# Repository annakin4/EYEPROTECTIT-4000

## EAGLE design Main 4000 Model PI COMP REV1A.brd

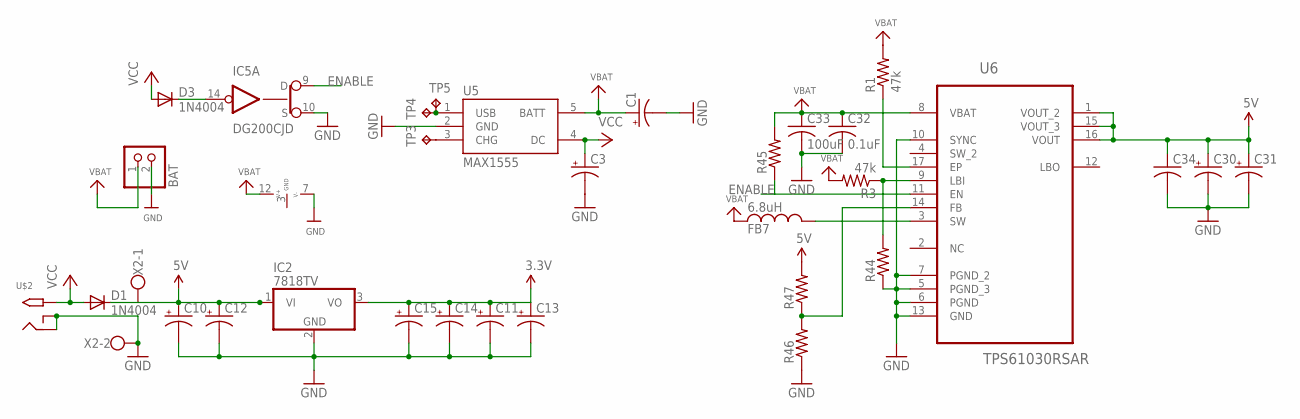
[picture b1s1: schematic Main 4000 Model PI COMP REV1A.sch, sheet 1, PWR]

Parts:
BAT: JST_2PIN-SMT-RA; JST-PH-2-SMT-RA
C1, C3, C11, C12, C14, C15, C30, C31: CPOL-USE1.8-4; E1,8-4
C10, C13: CPOL-USE2.5-6; E2,5-6
C32: 0.1uF; C0805
C33: 100uF; C0805
C34: C-USC0805; C0805
D1, D3: 1N4004; DO41-10
FB7: 6.8uH; SMD0805-A
IC2: 7818TV; TO220V
IC5: DG200CJD; SO14
R1, R3: 47k; R0805
R44, R45, R46, R47: R-US_R0805; R0805
TP3, TP4, TP5: TPTP20SQ; TP20SQ
U5: MAX1555; SOT23-5
U6: TPS61030RSAR; QFN65P400X400X100-17N
U$2: 2.1MMJACKTHM; PJ-102A
X2: W237-102

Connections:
3.3V: C11.+, C13.+, C14.+, C15.+, IC2.3 (VO); also elsewhere on the board
5V: C10.+, C12.+, C30.+, C31.+, C34.1, D1.C, IC2.1 (VI), R47.2, U6.1 (VOUT_2), U6.15 (VOUT_3), U6.16 (VOUT), X2.1; also elsewhere on the board
ENABLE: IC5.9 (D), R45.1, U6.11 (EN)
FB: R46.2, R47.1, U6.14 (FB)
GND: BAT.2 (1), C1.-, C3.-, C10.-, C11.-, C12.-, C13.-, C14.-, C15.-, C30.-, C31.-, C32.2, C33.2, C34.2, IC2.2 (GND), IC5.3 (GND), IC5.7 (V-), IC5.10 (S), R44.1, R46.1, U5.2 (GND), U6.5 (PGND_3), U6.6 (PGND), U6.7 (PGND_2), U6.10 (SYNC), U6.13 (GND), U$2.RING, U$2.RING_SW, X2.2; also elsewhere on the board
unnamed: TP3.TP, U5.3 (CHG)
unnamed: TP4.TP, TP5.TP, U5.1 (USB)
unnamed: D3.C, IC5.14 (IN)
unnamed: FB7.P$2 (2), U6.3 (SW)
unnamed: R1.1, U6.17 (EP)
unnamed: R3.1, R44.2, U6.9 (LBI)
VBAT: BAT.1 (2), C1.+, C32.1, C33.1, FB7.P$1 (1), IC5.12 (V+), R1.2, R3.2, R45.2, U5.5 (BATT), U6.8 (VBAT); also elsewhere on the board
VCC: C3.+, D1.A, D3.A, U5.4 (DC), U$2.TIP

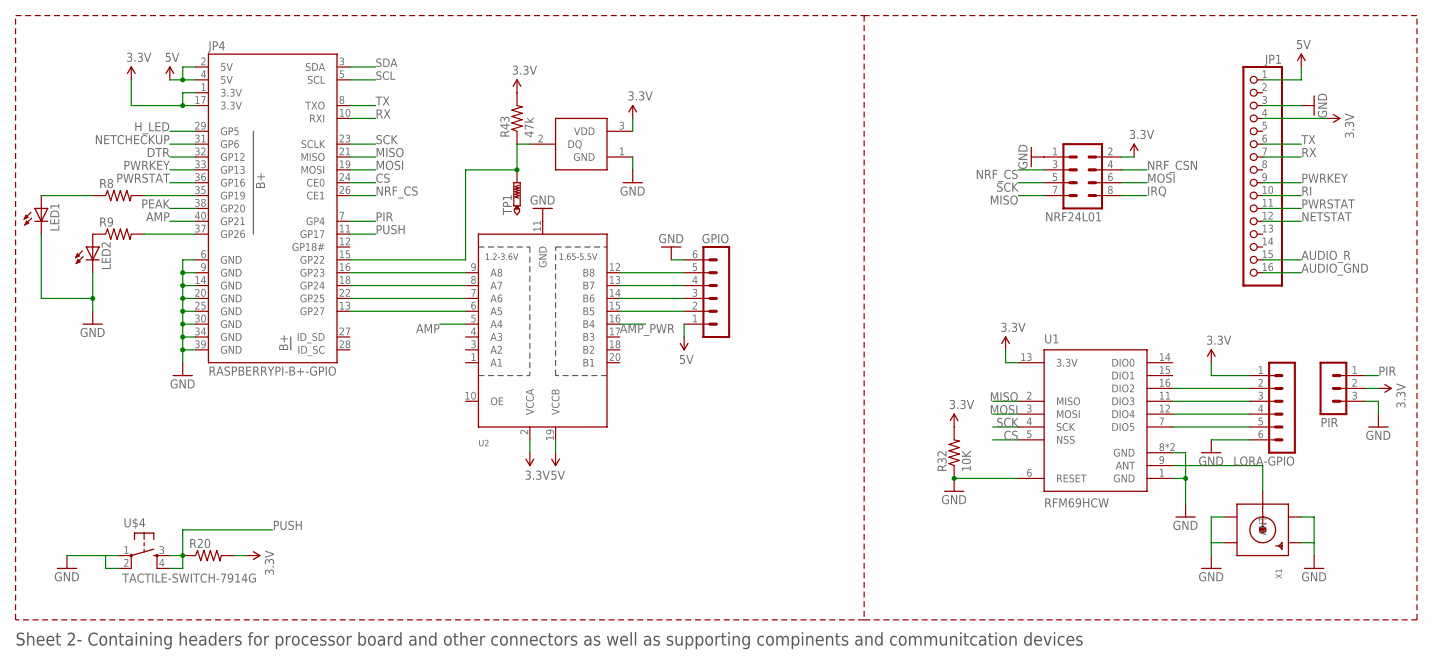
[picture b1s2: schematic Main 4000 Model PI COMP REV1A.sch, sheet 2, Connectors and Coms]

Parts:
GPIO: MA06-1
JP1: PINHD-1X16; 1X16
JP4: RASPBERRYPI-B+-GPIO; 2X20-SHROUDED
LED1, LED2: LED5MM
LORA-GPIO: MA06-1
NRF24L01: MA04-2
PIR: MA03-1
R8, R9, R20: R-US_R0805; R0805
R32: 10K; R0805
R43: 47k; R0805
TP1: PTR1PAD1-13; P1-13
U1: RFM69HCW; RFM69HCW-XXXS2
U2: TXB0108PWR; TSSOP20
U$4: TACTILE-SWITCH-7914G; 7914G
U$11: DS18B20Z; TO92
X1: SMACONNECTOR_EDGE; SMA_EDGELAUNCH

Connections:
3.3V: JP1.4, JP4.1 (3.3V), JP4.17 (3.3V), LORA-GPIO.1, NRF24L01.2, PIR.2, R20.2, R32.2, R43.2, U1.13 (3.3V), U2.2 (VCCA), U$11.3 (VDD); also elsewhere on the board
5V: GPIO.1, JP1.1, JP4.2 (5V), JP4.4 (5V), U2.19 (VCCB); also elsewhere on the board
AMP: JP4.40 (GP21), U2.5 (A4)
AMP_PWR: U2.16 (B4); also elsewhere on the board
AUDIO_GND: JP1.16; also elsewhere on the board
AUDIO_R: JP1.15; also elsewhere on the board
CS: JP4.24 (CE0), U1.5 (NSS)
DTR: JP4.32 (GP12)
GND: GPIO.6, JP1.3, JP4.6 (GND), JP4.9 (GND), JP4.14 (GND), JP4.20 (GND), JP4.25 (GND), JP4.30 (GND), JP4.34 (GND), JP4.39 (GND), LED1.K (C), LED2.K (C), LORA-GPIO.6, NRF24L01.1, PIR.3, R32.1, U1.1 (GND), U1.6 (RESET), U1.8 (GND), U1.10 (GND), U2.11 (GND), U$4.1, U$4.2, U$11.1 (GND), X1.GND@1 (GND4), X1.GND@2 (GND3), X1.GND@3 (GND2), X1.GND@4 (GND1); also elsewhere on the board
H_LED: JP4.29 (GP5); also elsewhere on the board
IRQ: NRF24L01.8
LED1: JP4.35 (GP19), R8.2
LED2: JP4.37 (GP26), R9.2
MISO: JP4.21 (MISO), NRF24L01.7, U1.2 (MISO)
MOSI: JP4.19 (MOSI), NRF24L01.6, U1.3 (MOSI)
unnamed: LORA-GPIO.5, U1.7 (DIO5)
unnamed: U1.9 (ANT), X1.P (ANT)
unnamed: LORA-GPIO.4, U1.12 (DIO4)
unnamed: LORA-GPIO.3, U1.11 (DIO3)
unnamed: LORA-GPIO.2, U1.16 (DIO2)
unnamed: LED2.A, R9.1
unnamed: JP4.16 (GP23), U2.9 (A8)
unnamed: JP4.18 (GP24), U2.8 (A7)
unnamed: JP4.22 (GP25), U2.7 (A6)
unnamed: JP4.13 (GP27), U2.6 (A5)
unnamed: LED1.A, R8.1
unnamed: GPIO.2, U2.15 (B5)
unnamed: GPIO.3, U2.14 (B6)
unnamed: GPIO.4, U2.13 (B7)
unnamed: GPIO.5, U2.12 (B8)
unnamed: JP4.15 (GP22), R43.1, TP1.TP, U$11.2 (DQ)
NETCHECKUP: JP4.31 (GP6)
NETSTAT: JP1.12
NRF_CS: JP4.26 (CE1), NRF24L01.3
NRF_CSN: NRF24L01.4
PEAK: JP4.38 (GP20); also elsewhere on the board
PIR: JP4.7 (GP4), PIR.1
PUSH: JP4.11 (GP17), R20.1, U$4.3, U$4.4
PWRKEY: JP1.9, JP4.33 (GP13)
PWRSTAT: JP1.11, JP4.36 (GP16)
RI: JP1.10
RX: JP1.7, JP4.10 (RXI)
SCK: JP4.23 (SCLK), NRF24L01.5, U1.4 (SCK)
SCL: JP4.5 (SCL); also elsewhere on the board
SDA: JP4.3 (SDA); also elsewhere on the board
TX: JP1.6, JP4.8 (TXO)

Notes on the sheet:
Sheet 2- Containing headers for processor board and other connectors as well as supporting compinents and communitcation devices

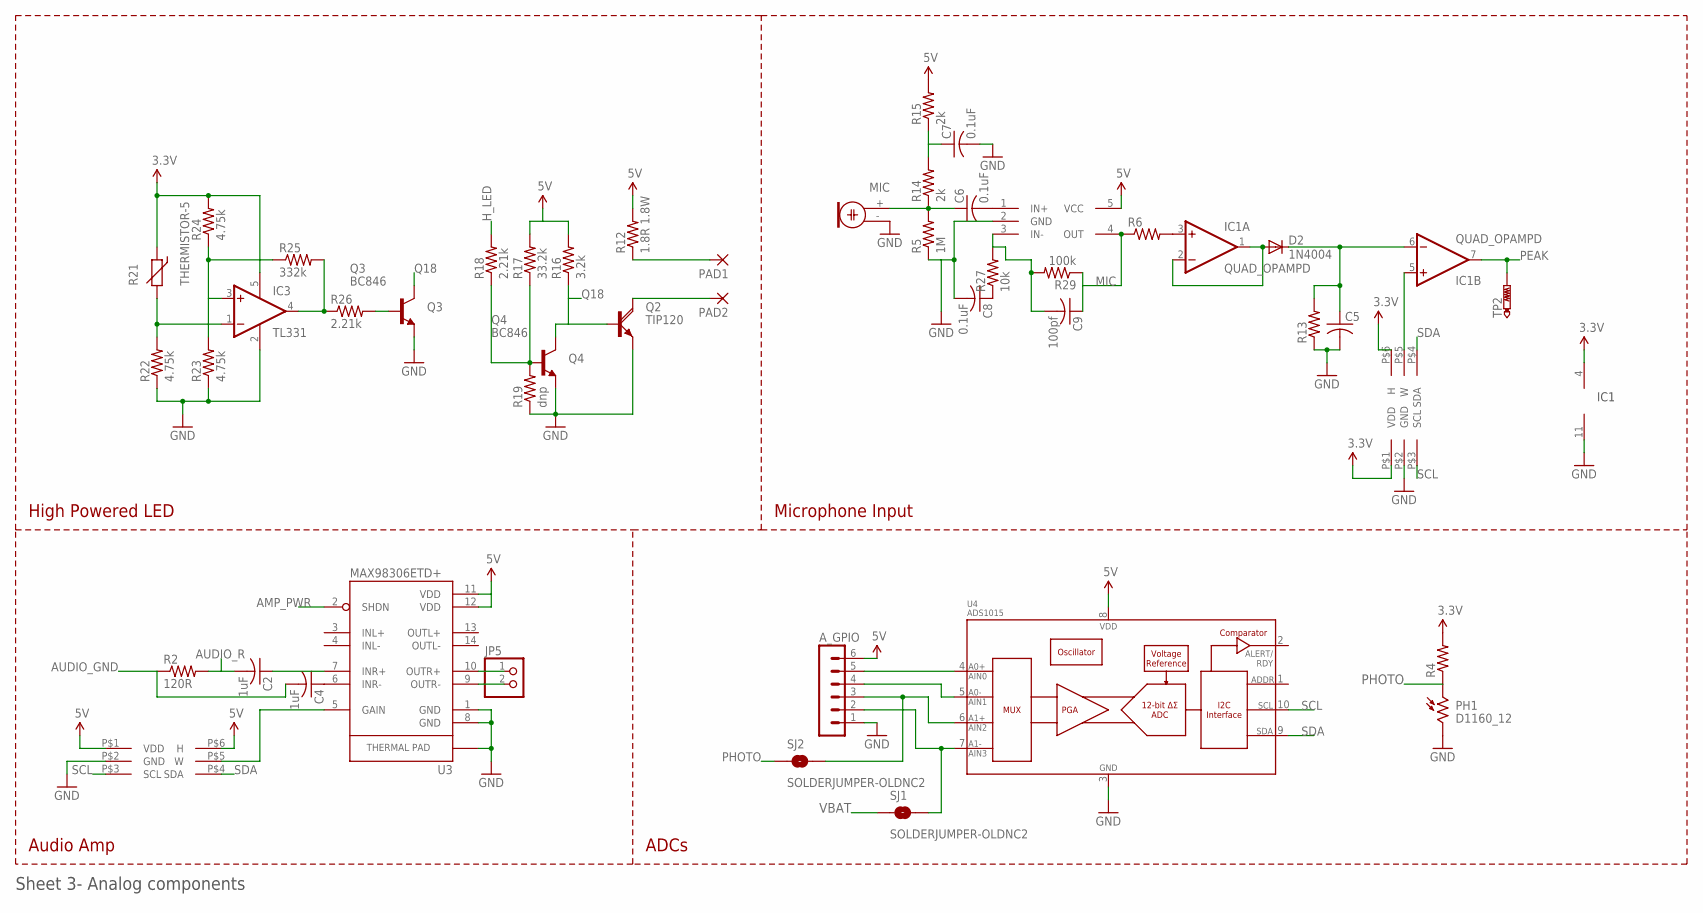
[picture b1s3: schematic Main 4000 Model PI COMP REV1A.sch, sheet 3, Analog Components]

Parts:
A_GPIO: MA06-1
C2, C4: 1uF; C0805
C5: C-USC0805K; C0805K
C6, C7, C8: 0.1uF; C0805
C9: 100pf; C0805
D2: 1N4004; DO41-10
IC1: QUAD_OPAMPD; SO14
IC3: TL331; DBV-R-PDSO-G5
JP5: PINHD-1X2; 1X02
MIC: ELECTRET; 9.7ELECTRET
PAD1, PAD2: 3,81/1,4
PH1: D1160_12; D11XX
Q2: TIP120; TO220AH
Q3, Q4: BC846; SOT23
R2: 120R; R0805
R4, R6, R13: R-US_R0805; R0805
R5: 1M; R0805
R12: 1.8R 1.8W; VMTB60
R14, R15: 2k; R0805
R16: 3.2k; R0805
R17: 33.2k; R0805
R18, R26: 2.21k; R0805
R19: dnp; R0805
R21: THERMISTOR-5; R-5
R22, R23, R24: 4.75k; R0805
R25: 332k; R0805
R27: 10k; R0805
R29: 100k; R0805
SJ1, SJ2: SOLDERJUMPER-OLDNC2; SJ_2S-NOTRACE
TP2: PTR1PAD1-13; P1-13
U3: MAX98306ETD+; 14-TDFN
U4: ADS1015; MSOP10
U$1, U$5: TPL0401A/B; SC-70
U$3: MAX4466; SOT23-5L

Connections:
3.3V: IC1.4 (V+), IC3.5 (V+), R4.2, R21.1, R24.2, U$5.P$1 (VDD), U$5.P$6 (H); also elsewhere on the board
5V: A_GPIO.6, R12.2, R15.2, R16.2, R17.2, U3.11 (VDD), U3.12 (VDD), U4.8 (VDD), U$1.P$1 (VDD), U$1.P$6 (H), U$3.5 (VCC); also elsewhere on the board
AMP_PWR: U3.2 (SHDN); also elsewhere on the board
AUDIO_GND: C4.2, R2.1; also elsewhere on the board
AUDIO_R: C2.2, R2.2; also elsewhere on the board
GND: A_GPIO.1, C5.2, C7.2, C8.2, IC1.11 (V-), IC3.2 (GND), MIC.- (1), PH1.2, Q2.E, Q3.2 (E), Q4.2 (E), R5.1, R13.1, R19.1, R22.1, R23.1, U3.1 (GND), U3.8 (GND), U3.15 (GND), U4.3 (VSS), U$1.P$2 (GND), U$3.2 (GND), U$5.P$2 (GND); also elsewhere on the board
H_LED: R18.2; also elsewhere on the board
MIC: C9.1, R6.1, R29.1, U$3.4 (OUT)
unnamed: C5.1, D2.C, IC1.6 (-IN), R13.2
unnamed: C6.1, MIC.+ (2), R5.2, R14.1
unnamed: IC1.5 (+IN), U$5.P$5 (W)
unnamed: C2.1, U3.7 (INR+)
unnamed: C4.1, U3.6 (INR-)
unnamed: A_GPIO.5, U4.4 (AIN0)
unnamed: A_GPIO.4, U4.5 (AIN1)
unnamed: A_GPIO.3, SJ2.2, U4.6 (AIN2)
unnamed: A_GPIO.2, SJ1.2, U4.7 (AIN3)
unnamed: IC1.3 (+IN), R6.2
unnamed: D2.A, IC1.1 (OUT), IC1.2 (-IN)
unnamed: JP5.2, U3.9 (OUTR-)
unnamed: JP5.1, U3.10 (OUTR+)
unnamed: C6.2, U$3.1 (IN+)
unnamed: C7.1, R14.2, R15.1
unnamed: U3.5 (GAIN), U$1.P$5 (W)
unnamed: PAD2.1, Q2.C
unnamed: PAD1.1, R12.1
unnamed: C8.1, R27.1
unnamed: Q4.1 (B), R17.1, R18.1, R19.2
unnamed: IC3.1 (-IN), R21.2, R22.2
unnamed: IC3.3 (+IN), R23.2, R24.1, R25.1
unnamed: IC3.4 (OUT), R25.2, R26.1
unnamed: Q3.1 (B), R26.2
unnamed: C9.2, R27.2, R29.2, U$3.3 (IN-)
PEAK: IC1.7 (OUT), TP2.TP; also elsewhere on the board
PHOTO: PH1.1, R4.1, SJ2.1; also elsewhere on the board
Q18: Q2.B, Q3.3 (C), Q4.3 (C), R16.1
SCL: U4.10 (SCL), U$1.P$3 (SCL), U$5.P$3 (SCL); also elsewhere on the board
SDA: U4.9 (SDA), U$1.P$4 (SDA), U$5.P$4 (SDA); also elsewhere on the board
VBAT: SJ1.1; also elsewhere on the board

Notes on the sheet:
High Powered LED
Audio Amp
ADCs
Microphone Input
Sheet 3- Analog components
IC1

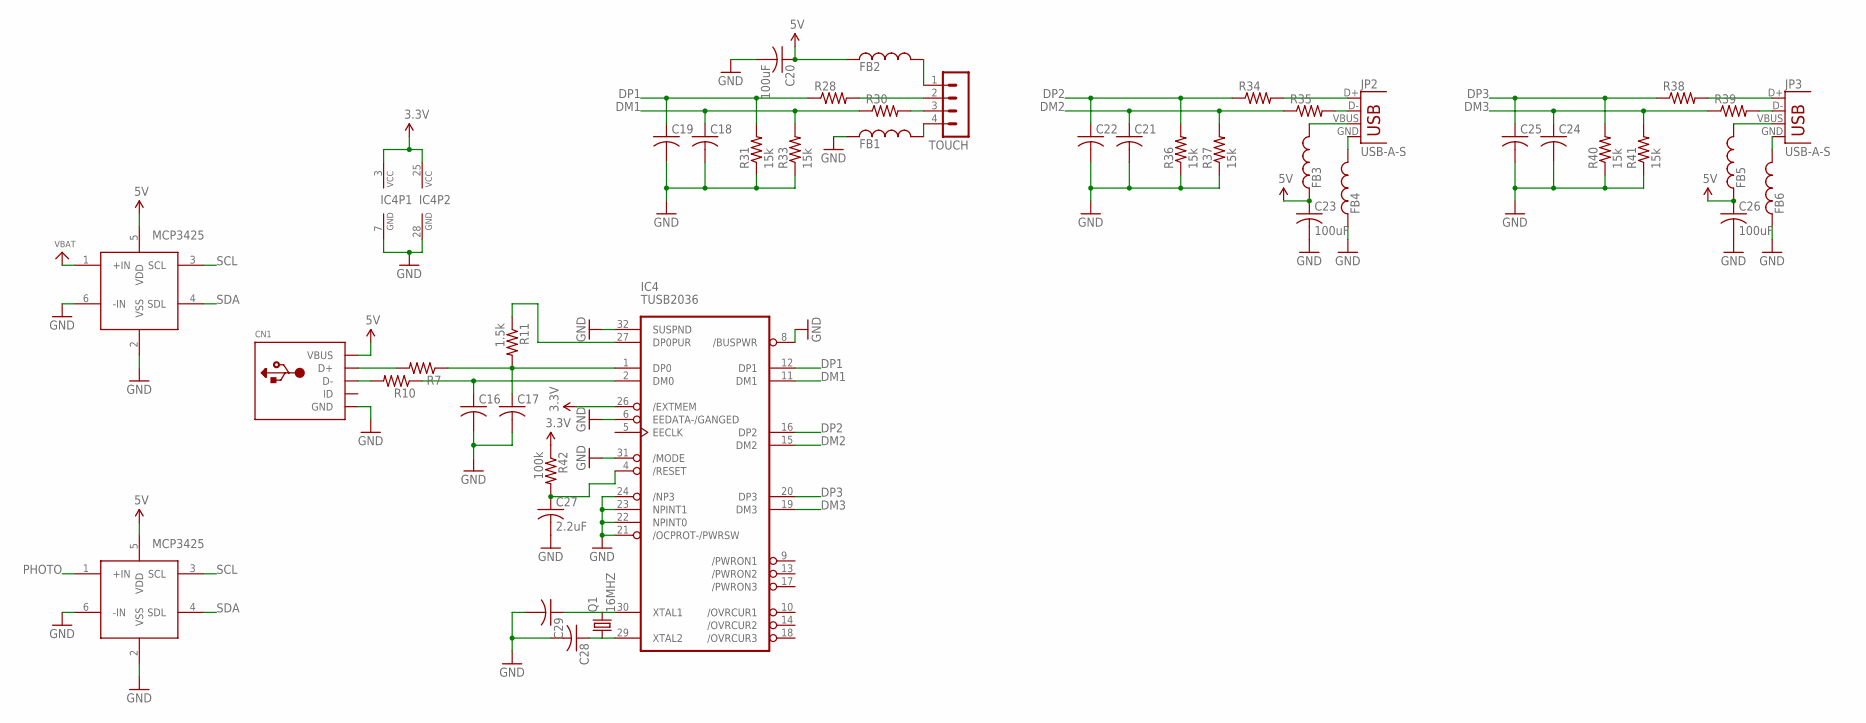
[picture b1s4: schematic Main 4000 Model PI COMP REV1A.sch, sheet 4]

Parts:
C16, C17, C18, C19, C21, C22, C24, C25, C28, C29: C-USC0805; C0805
C20, C23, C26: 100uF; C0805
C27: 2.2uF; C0805
CN1: USBMOLEX; USB-MINIB-THM-MOLEX
FB1, FB2, FB3, FB4, FB5, FB6: FB1206
IC4: TUSB2036; LQFP32
JP2, JP3: USB-A-S
Q1: 16MHZ; HC49UP
R7, R10, R28, R30, R34, R35, R38, R39: R-US_R0805; R0805
R11: 1.5k; R0805
R31, R33, R36, R37, R40, R41: 15k; R0805
R42: 100k; R0805
TOUCH: MA04-1
U$6, U$8: MCP3425SOT; SOT23-6

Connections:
3.3V: IC4.3 (VCC), IC4.25 (VCC), IC4.26 (/EXTMEM), R42.1; also elsewhere on the board
5V: C20.1, C23.1, C26.1, CN1.VBUS, FB2.1, FB3.1, FB5.1, U$6.5 (VDD), U$8.5 (VDD); also elsewhere on the board
DM1: C18.1, IC4.11 (DM1), R30.1, R33.2
DM2: C21.1, IC4.15 (DM2), R35.1, R37.2
DM3: C24.1, IC4.19 (DM3), R39.1, R41.2
DP1: C19.1, IC4.12 (DP1), R28.1, R31.2
DP2: C22.1, IC4.16 (DP2), R34.1, R36.2
DP3: C25.1, IC4.20 (DP3), R38.1, R40.2
GND: C16.2, C17.2, C18.2, C19.2, C20.2, C21.2, C22.2, C23.2, C24.2, C25.2, C26.2, C27.2, C28.2, C29.2, CN1.GND, FB1.1, FB4.1, FB6.1, IC4.6 (EEDATA-/GANGED), IC4.7 (GND), IC4.8 (/BUSPWR), IC4.21 (/OCPROT-/PWRSW), IC4.22 (NPINT0), IC4.23 (NPINT1), IC4.24 (/NP3), IC4.28 (GND), IC4.31 (/MODE), IC4.32 (SUSPND), R31.1, R33.1, R36.1, R37.1, R40.1, R41.1, U$6.2 (VSS), U$6.6 (-IN), U$8.2 (VSS), U$8.6 (-IN); also elsewhere on the board
unnamed: R30.2, TOUCH.3
unnamed: JP2.D-, R35.2
unnamed: CN1.D-, R10.2
unnamed: CN1.D+, R7.2
unnamed: C17.1, IC4.1 (DP0), R7.1, R11.2
unnamed: C16.1, IC4.2 (DM0), R10.1
unnamed: IC4.27 (DP0PUR), R11.1
unnamed: JP2.D+, R34.2
unnamed: R28.2, TOUCH.2
unnamed: FB2.2, TOUCH.1
unnamed: FB1.2, TOUCH.4
unnamed: FB3.2, JP2.VBUS
unnamed: FB4.2, JP2.GND
unnamed: JP3.D-, R39.2
unnamed: JP3.D+, R38.2
unnamed: FB5.2, JP3.VBUS
unnamed: FB6.2, JP3.GND
unnamed: C29.1, IC4.30 (XTAL1), Q1.2
unnamed: C28.1, IC4.29 (XTAL2), Q1.1
unnamed: C27.1, IC4.4 (/RESET), R42.2
PHOTO: U$6.1 (+IN); also elsewhere on the board
SCL: U$6.3 (SCL), U$8.3 (SCL); also elsewhere on the board
SDA: U$6.4 (SDL), U$8.4 (SDL); also elsewhere on the board
VBAT: U$8.1 (+IN); also elsewhere on the board

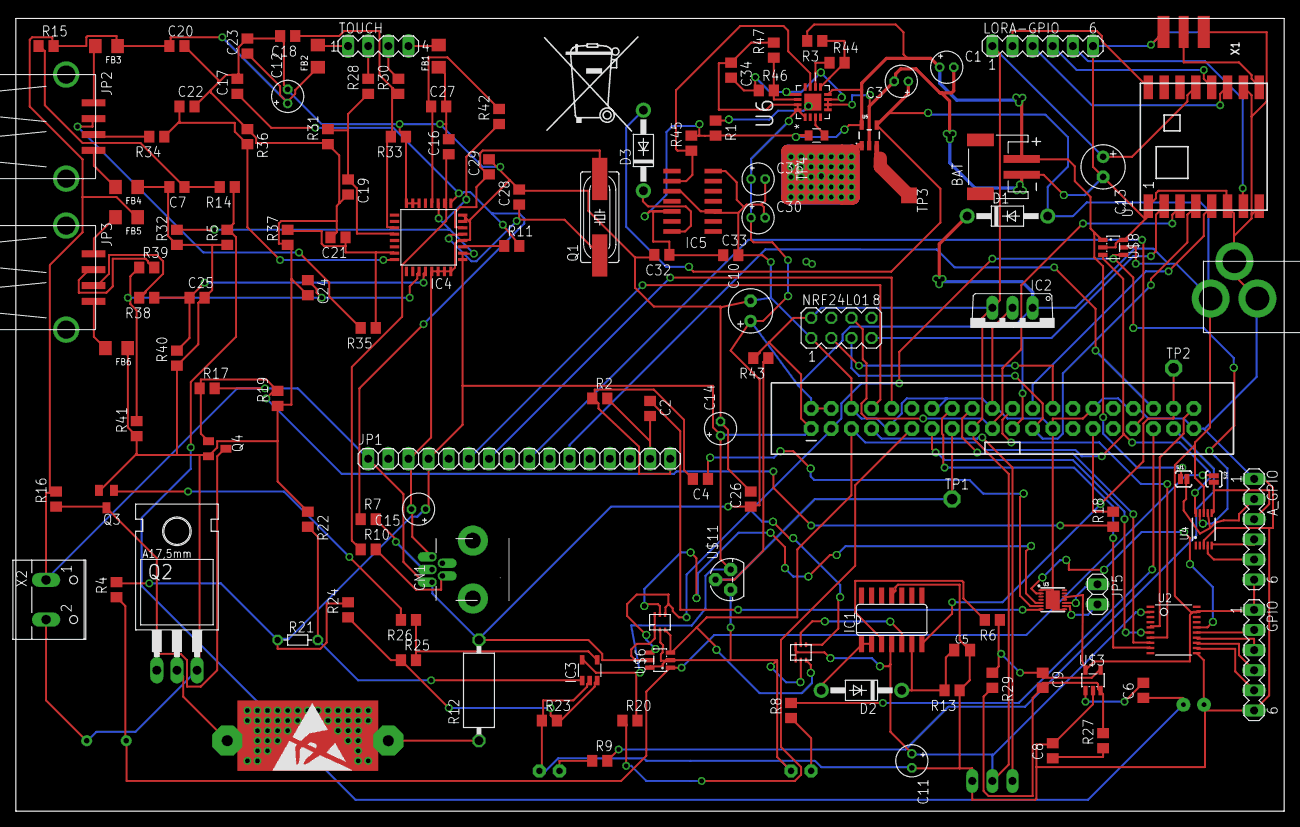
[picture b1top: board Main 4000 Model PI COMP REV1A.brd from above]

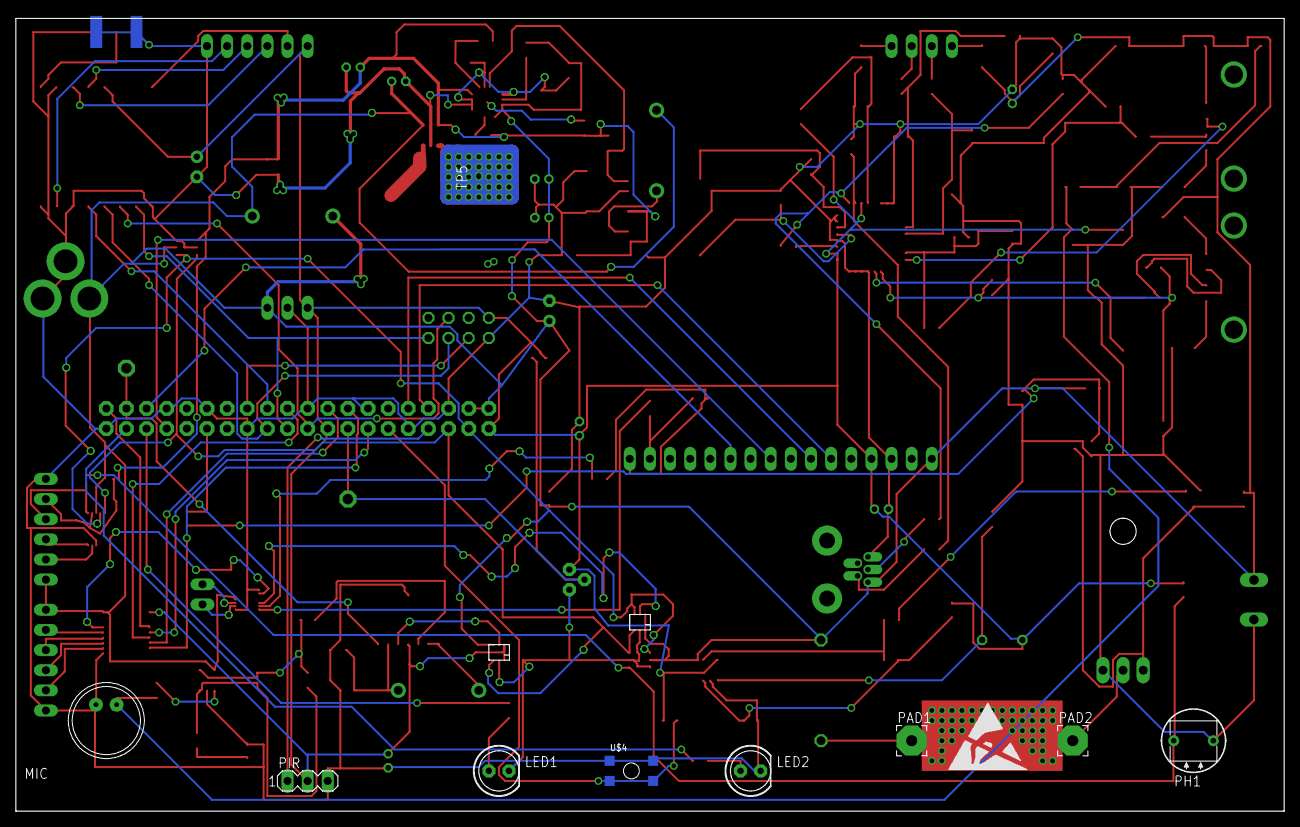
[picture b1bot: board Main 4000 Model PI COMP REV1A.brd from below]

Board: 2 copper layers, 159.9 x 99.9 mm, 145 parts (10 on the bottom side), 104 nets.

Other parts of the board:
U$13, U$14: ESD_10.00
U$15: MUELLTONNE

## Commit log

2016-07-07 First revision
2016-07-11 REV1A
    Added one wire, renamed
2016-07-12 Routed Pi version
2016-07-25 Added boost circuit
2016-07-25 Laid out booster circuit

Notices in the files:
parts and their libraries:
SparkFun-Connectors: Licensing: Creative Commons ShareAlike 4.0 International - https://creativecommons.org/licenses/by-sa/4.0
microbuilder: This work is placed in the public domain, and may be freely used for commercial and non-commercial work with the following conditions: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
